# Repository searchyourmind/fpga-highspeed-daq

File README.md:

# FPGA High-Speed DAQ — RTL simulation portfolio

**SystemVerilog · cocotb · Verilator · Python · Yosys · nextpnr (Lattice ECP5)**

A single-clock acquisition pipeline with ready/valid buffering, saturating gain, ring-buffer DMA and packetized host readback. **63 tests pass; 33 end-to-end scenarios match independent expected records.** DDR3 is a **behavioral model**; PCIe is a **custom transaction-level model**, not a hardware endpoint.

The waveform comes from an executed regression. [Full VCD](evidence/core/daq_top.vcd.gz) · [Trace provenance](portfolio/assets/evidence.json)

| Verified result | Evidence |
|---|---|
| **63/63 PASS**, zero failures/skips | 39 pytest + 24 cocotb; [actual clean-checkout log](evidence/core/verify.log) |
| **33/33 MATCH** | 15 baseline + 18 extended scenarios **within** those tests; [results](evidence/core/verification.json) |
| Independent checks detect six injected defects | [Mutation results and coverage limits](docs/VERIFICATION_REVIEW.md) |
| Generic synthesis: 1,447 flip-flops, no latches/loops | [Yosys evidence](evidence/core/synthesis/); 42-cell topological path |
| **ECP5 place and route: 57.3 MHz median Fmax** (5 seeds, LFE5U-25F); meets the 25 MHz board clock | [Board build, critical path, resources](fpga/README.md) |

### ECP5 baseline

The core is placed and routed for the Lattice LFE5U-25F on a [ULX3S board top](fpga/README.md) that takes descriptors over UART and keeps every input live. These are the numbers to beat:

- **Fmax 55.7 / 57.3 / 58.0 MHz** (min / median / max of 5 seeds); 2,017 LUT4, 1,315 FF, 2 block RAMs, 2 multipliers.
- **Critical path:** two hardware multipliers in one cycle, `seq × 73` in `sensor_source` feeding `× gain` in `stream_processor`.
- **DMA throughput:** one memory command in flight, so a word costs latency + 1 cycles to write and latency + 2 to read; 0.03 words per cycle at a 32-cycle latency. [Chart and table](fpga/README.md#dma-throughput-baseline-simulation)

The bitstream builds but has not been run on a board.

### Debugging findings

- **4 KiB crossing:** a packet starting at `0x1ff8` crossed a page. Bound payload length by page remainder; [original failing assertion](evidence/debug/boundary-before-fix.xml) retained.
- **Address boundary:** fixed rejection of the final legal 8-byte record at `2^64−8` by validating the last addressed byte.
- **Delayed delivery:** retained host tag ownership until data consumption, even after RTL completion.
- **False-success runner:** reject failed/stale/empty/skipped JUnit; a real failing fixture verifies the gate. [Review](docs/VERIFICATION_REVIEW.md)

### Reproduce

Requires Docker, Make and Python 3. Run from the repository root:

```sh
make tools
make verify                 # lint, 63 tests / 33 scenarios, generic synthesis
make timing                 # structural checks; no device delays or slack
make fpga-tools && make fpga  # ECP5 synthesis, place and route (5 seeds), bitstream
make fpga-test              # ULX3S board top, driven through its UART pins
make throughput             # DMA words per cycle against memory latency
```

Recorded versions: Verilator 5.040, cocotb 2.0.0, pytest 8.4.2, Yosys 0.33. [Commands, versions and clean-checkout scope](docs/REPRODUCING.md) · [Simulation benchmark](portfolio/assets/benchmarks.png)

### Explore the engineering

[Architecture and RTL modules](docs/architecture.md) · [Verification review](docs/VERIFICATION_REVIEW.md) · [Portfolio summary](portfolio/README.md) · [Resume bullets](docs/RESUME_BULLETS.md) · [Release summary](release/RELEASE_SUMMARY.md)

One descriptor is active at a time; capture finishes before readback. The source honors backpressure. No physical ADC, DDR PHY, real PCIe TLP/LCRC or measured hardware throughput is claimed; the ECP5 timing comes from nextpnr's model, not a board. [Interface contracts](docs/interface_contracts.md) · [Synthesis scope](synthesis/README.md)

### Separate PCB Rev 0.3.1 design study

The [Pi 5 FFC-to-M.2 carrier](hardware/reference_pcie_adapter/README.md) is **not the FPGA DAQ board**. Native CAD checks pass; engineering acceptance remains **FAIL**:

| Requirement | Retained result |
|---|---|
| Voltage: 3.135–3.465 V | 3.130447–3.487610 V; margins **−4.553 / −22.610 mV** |
| Thermal screen: ≤125 °C | **6/24 FAIL**; fine-grid worst **160.303 °C**, margin **−35.303 °C** |
| Differential impedance: 81–99 Ω | Broad high corner **106.126 Ω**, margin **−7.126 Ω** |

These are modeled rejection indicators, not measurements or qualified operating conditions. [All cases and root causes](hardware/reference_pcie_adapter/INDEPENDENT_REVIEW.md) · [Pass/fail matrix](docs/REQUIREMENTS_MATRIX.md). No fabrication, purchases or physical validation. Published **as a simulation portfolio with a separate design study**. Local verification evidence is retained; live CI status is available in [GitHub Actions](https://github.com/searchyourmind/fpga-highspeed-daq/actions).

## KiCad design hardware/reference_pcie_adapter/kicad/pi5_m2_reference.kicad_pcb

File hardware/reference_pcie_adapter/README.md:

# Pi 5 FFC to M.2 M-key reference adapter - Rev 0.3.1

**DESIGN REVIEW DRAFT - NOT RELEASED FOR MANUFACTURE.** This is a separate PCB exercise, not a board implementing the DAQ RTL. No board, FPGA, SSD or Pi was purchased, fabricated, powered or tested.

Read the current [INDEPENDENT_REVIEW.md](INDEPENDENT_REVIEW.md) for retained failures and corrected minimum-copper thermal results. [ENGINEERING_REVIEW.md](ENGINEERING_REVIEW.md) retains the preceding detailed review. The current [four-page review PDF](../../portfolio/Independent_Release_Review.pdf) summarizes both project scopes. [BOM_selected.csv](BOM_selected.csv) records 30 manufacturer part selections, conditional approvals and the legacy FFC hold.

Published [CAD views and all numerical cases](../../evidence/pcb/) are preserved separately from ignored regenerated `outputs/`. The board is frozen; no redesign occurred during portfolio finalization.

## Implemented and checked
- Native KiCad 9 schematic and 80 x 78 mm, four-layer board. 30 electrical references, four board-only mounting holes, M.2 support and a corrected 22 x 42 mm card envelope.
- 424 trace/via objects, two filled inner GND planes plus outer power-area GND spreaders. Eight QFN thermal vias and four added TX return vias.
- **ERC 0, geometric DRC 0, unconnected 0, schematic parity 0.** Pin contracts and saved differential geometry pass. Zero planar pair skew excludes connector/via electrical effects.
- Actual schematic PDF, board SVG, native 3D render and DRAFT-only Gerber/drill exports in `outputs/`. Some 3D bodies are unavailable. Final drill report: 92 plated / 7 unplated holes, including H5 center clearance.
- 108 power DC/AC cases; official TPS62130A nominal and loaded-corner startup/load-event/shutdown models; 126 copper load distributions; 24 thermal cases; actual mechanical/filled-plane checks; 2D field solution with convergence checks. `results/engineering-check-summary.json` separates numerical execution from failed design margins.

## Results that prevent release
| Area | Current conclusion |
|---|---|
| Voltage | Nominal and loaded external-component A transients pass, but conservative composite range 3.130447-3.487610 V exceeds the 3.135-3.465 V target. |
| Heat | Corrected 30 um minimum-copper screen: 6/24 FAIL. Fine-grid worst 160.302515 C, margin -35.302515 C against 125 C. Original 35 um five failures and 159.381 C estimate retained. Extrapolated rejection, not sustainable operation. No 2 A continuous rating. |
| SI | Nominal 93.94 ohm. Broad assumed process corners 83.29-106.13 ohm exceed target. Four width candidates under the original broad assumptions fail; tighter tolerances are not accepted as closure. |
| Components | Real candidate MPNs recorded. MLCC effective capacitance, hot/fault inductor behavior, superseded FFC/cable and final connector approval remain open. |
| Mechanics/assembly | Planar envelope passes. Actual SSD, height tolerances, screw engagement, enclosure and via-in-pad assembly remain open. |

## Electrical scope
External regulated, current-limited 5 V enters J3. The 2 A SSD load is a design stress target, not an approved rating. At 4.65 V input and assumed 85% efficiency, its power-core input budget is approximately 1.684 A. Actual cable/mating contacts require approval. The unkeyed input has no reverse-polarity or hot-plug protection.

U1 is **TPS62130A**, with 31.6k/10k 0.1% feedback (3.328 V nominal), 2.2 uH and two nominal 22 uF output capacitors. The A suffix is required: PG pulls low on EN shutdown while VIN remains present. Its official A-model transient is distinct from the older, separate hypothetical 12 V power-tree experiment.

FFC pins 1/2 feed detection only through 3.6k/6.8k; they do not join EXT_5V. All grounds share the reference plane. PWR_EN has a 100k pulldown. PG drives NC7SB3157 CLKREQ isolation; Q1 gates PERST, Q2/Q3 translate open-drain wake. Full missing-supply and IO sequencing is not qualified. J4 external SUSCLK is DNP by default; a selected SSD must not require it for the baseline.

M.2 host-side pin 69 is grounded as in the official Pi reference. Pi RX_P connects to PETP0 pin 43; Pi TX_P to PERP0 pin 49. No additional AC coupling capacitors are inserted; actual endpoint/cable requirements remain an approval item.

The custom TE land pattern follows G-2199230 Rev B3 sheet 3. **1-2199230-4 is M-key; unprefixed 2199230-4 is E-key and must not be substituted.** The drawing and part-specific current approval are distinct.

## Stackup and SI scope
Reference JLC04161H-3313: nominal 1.6 mm, outer copper 35 um, outer prepreg 99.4 um/Er 4.1, inner copper 15.2 um and core 1.265 mm/Er 4.6. These are preliminary design inputs, not a vendor commitment. Adjacent inner planes reference F.Cu/B.Cu pairs. Trunks use 0.14 mm width / 0.152 mm gap; connector/via breakouts expand.

The new quasi-static 2D solver includes an assumed mask and is a screening result. The old 92.11 ohm empirical formula in `outputs/impedance-estimate.json` is a historical approximation. Neither result establishes connector/cable loss, via 3D behavior, eye diagrams, TDR or PCIe compliance. Actual plane projection has no unintended reference voids; TX ground-return vias are within 0.891 mm of each transition.

## Sources, reproduction and constraints
`design.py` is the electrical source; `build.py` creates native CAD; `apply_routing.py` replays `routing/tracks.json`. `make pcb` checks current CAD. `make pcb-rebuild` explicitly regenerates it; preserve future manual changes first.

`make analysis-tools` builds isolated dependencies. `make pcb-engineering` runs the entire numerical review and creates the review PDF; it can take tens of minutes. `make pcb-engineering-check` checks retained evidence. `make pcb-draft` emits review-only files. No command orders hardware or pushes GitHub.

Detailed sources, failed attempts, limits and next work are in `ENGINEERING_REVIEW.md`, `docs/PROGRESS.md` and `NEXT_SESSION.md`. The actual model files are fetched from TI and excluded from the portable archive. Cadence hands-on remains **NOT COMPLETED**.

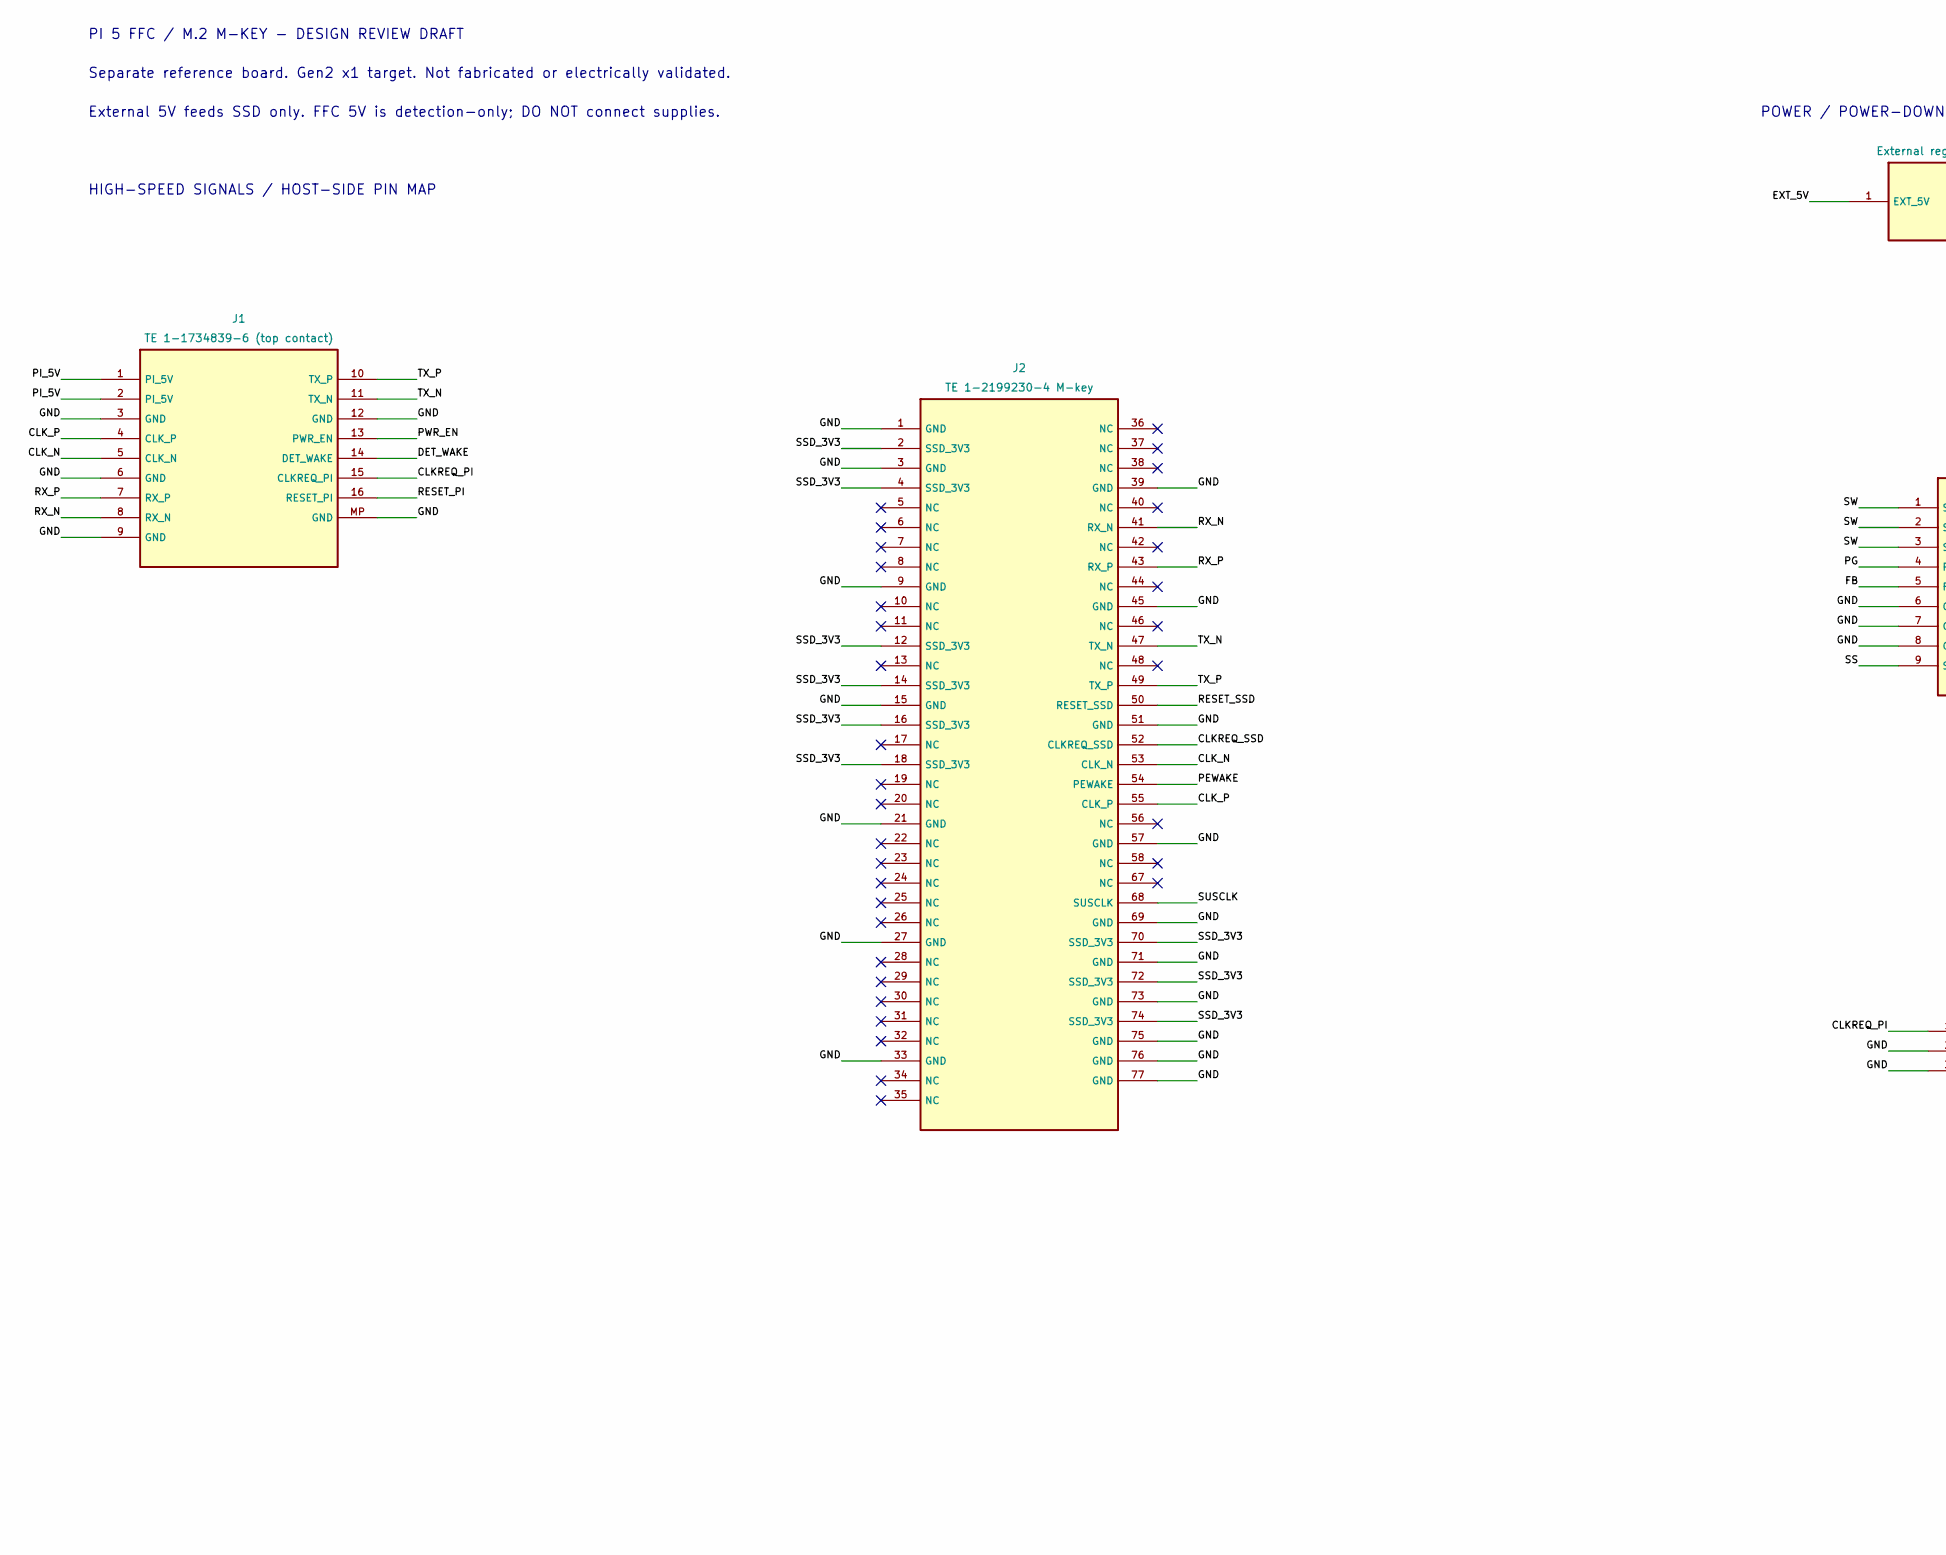
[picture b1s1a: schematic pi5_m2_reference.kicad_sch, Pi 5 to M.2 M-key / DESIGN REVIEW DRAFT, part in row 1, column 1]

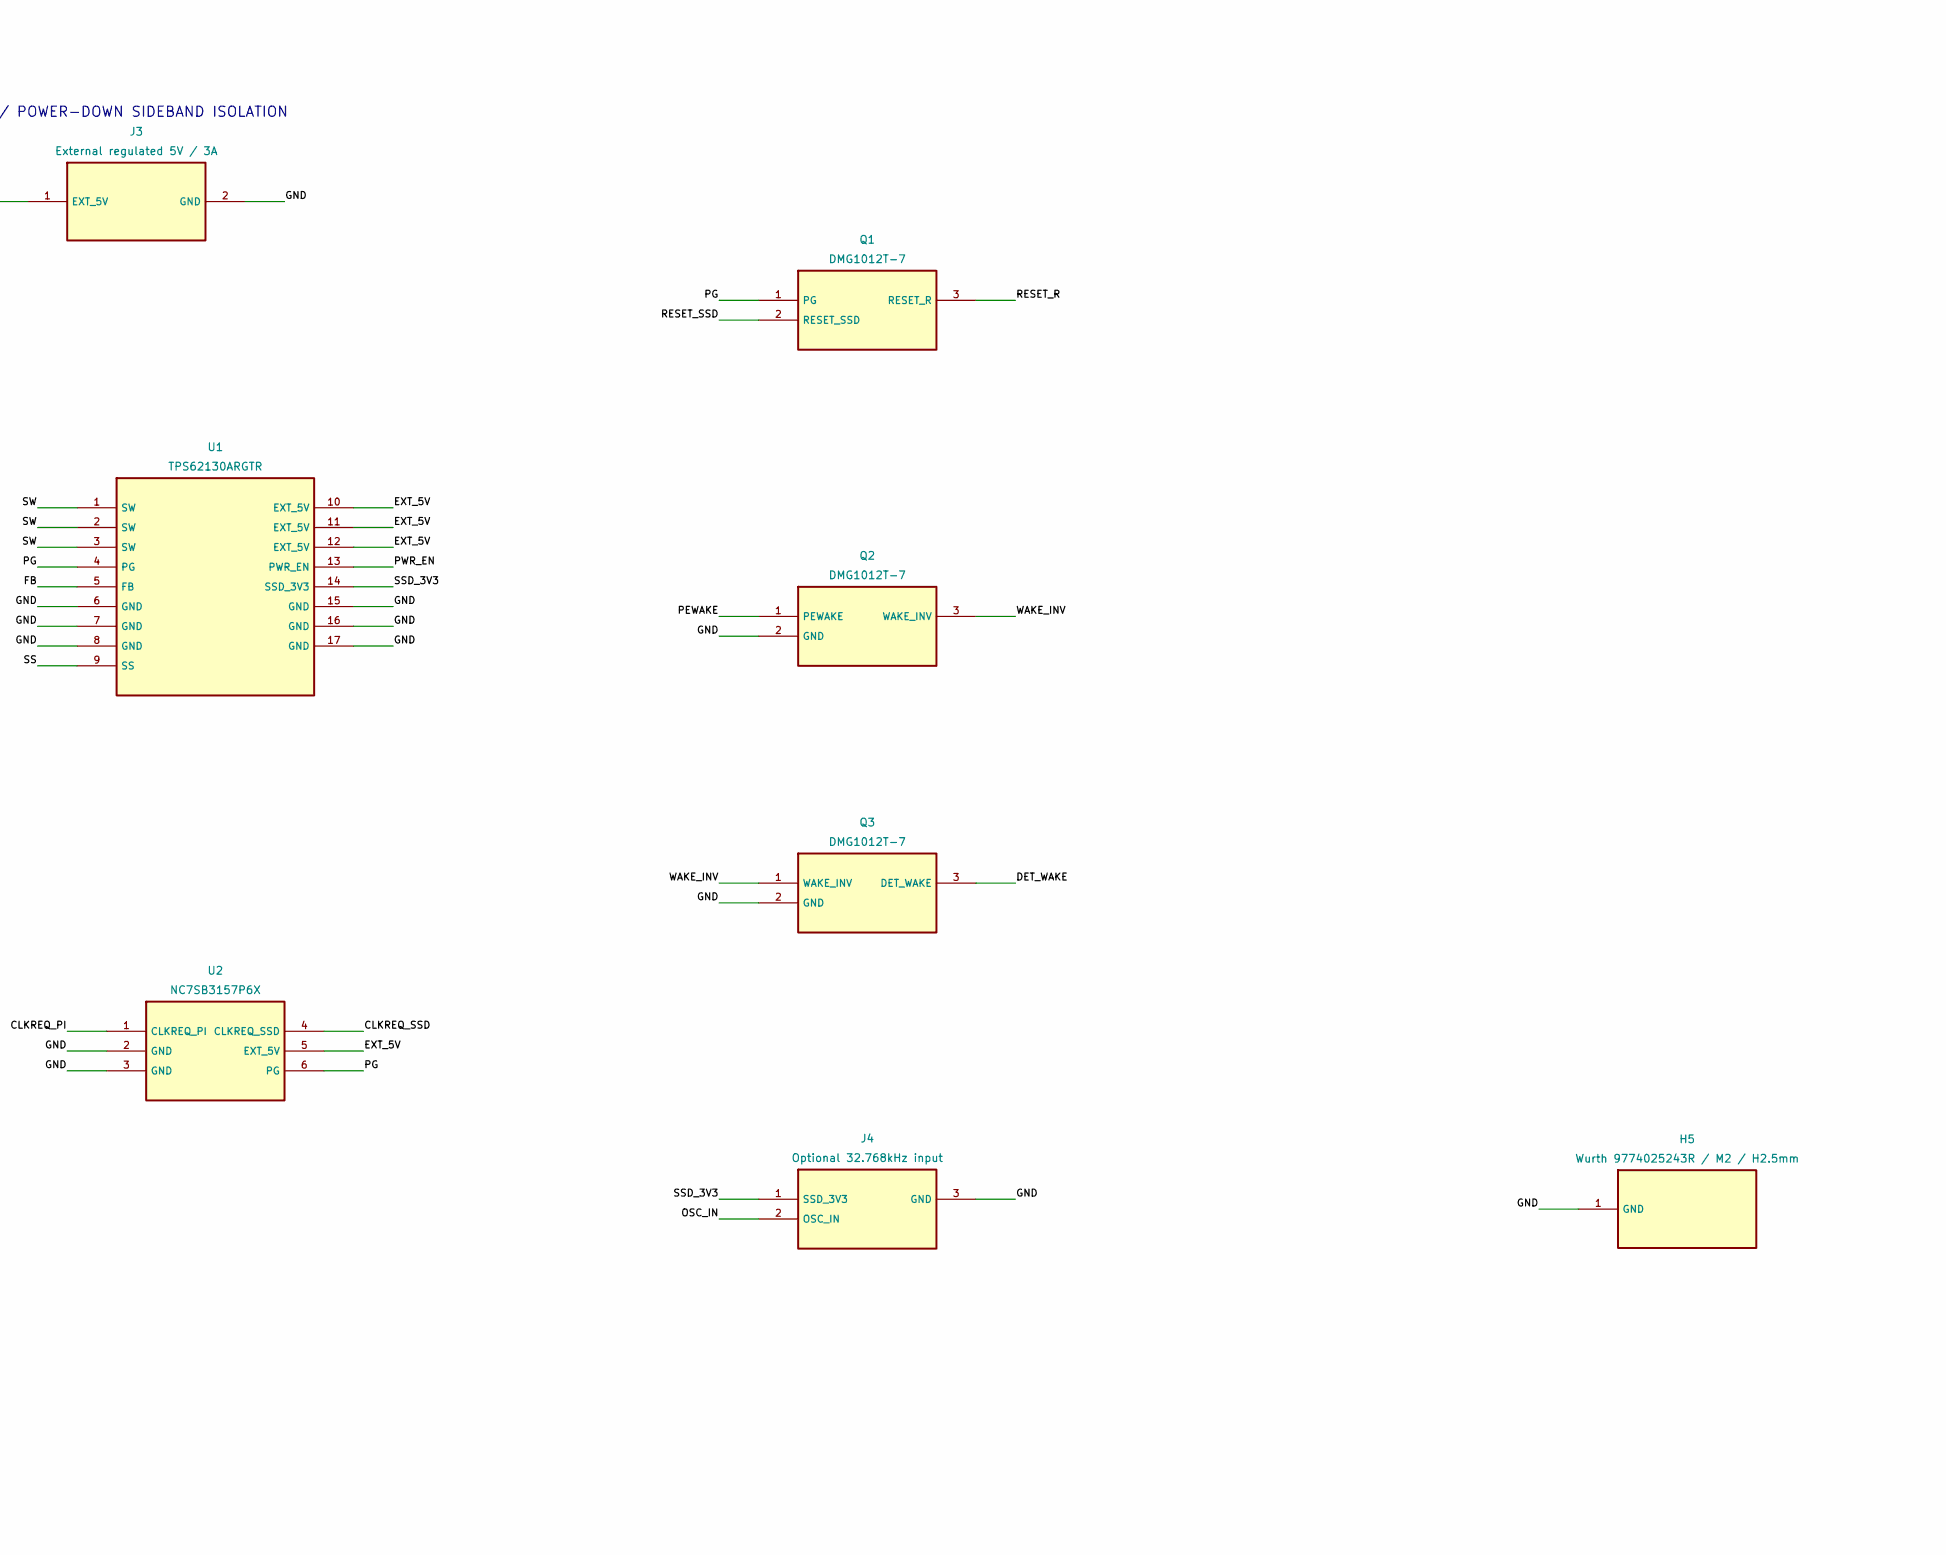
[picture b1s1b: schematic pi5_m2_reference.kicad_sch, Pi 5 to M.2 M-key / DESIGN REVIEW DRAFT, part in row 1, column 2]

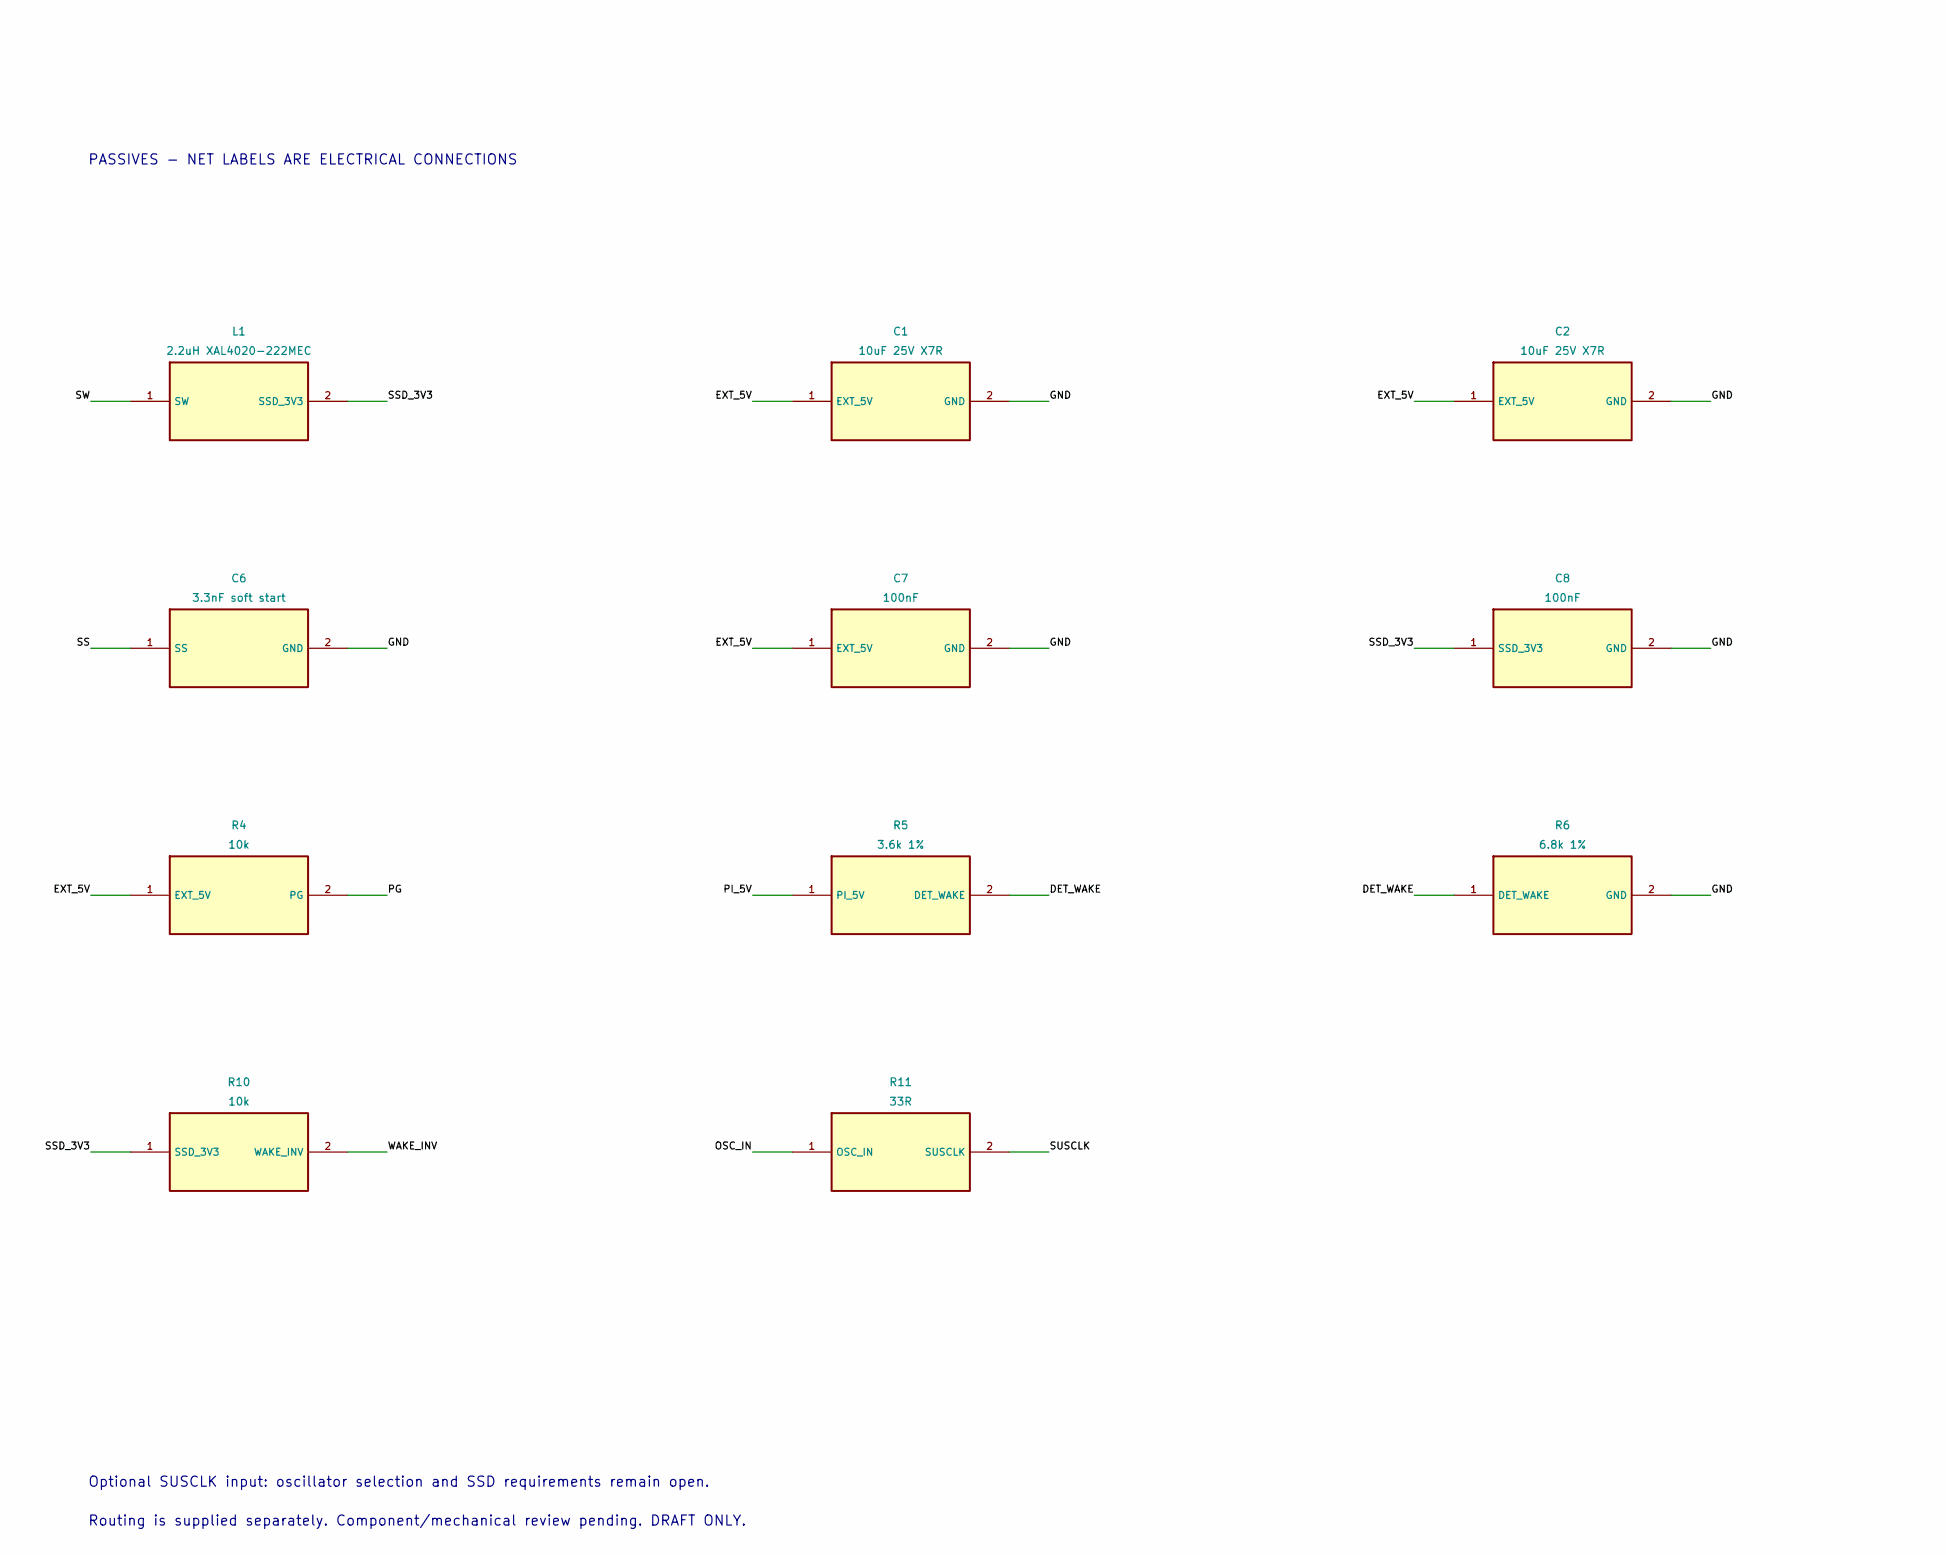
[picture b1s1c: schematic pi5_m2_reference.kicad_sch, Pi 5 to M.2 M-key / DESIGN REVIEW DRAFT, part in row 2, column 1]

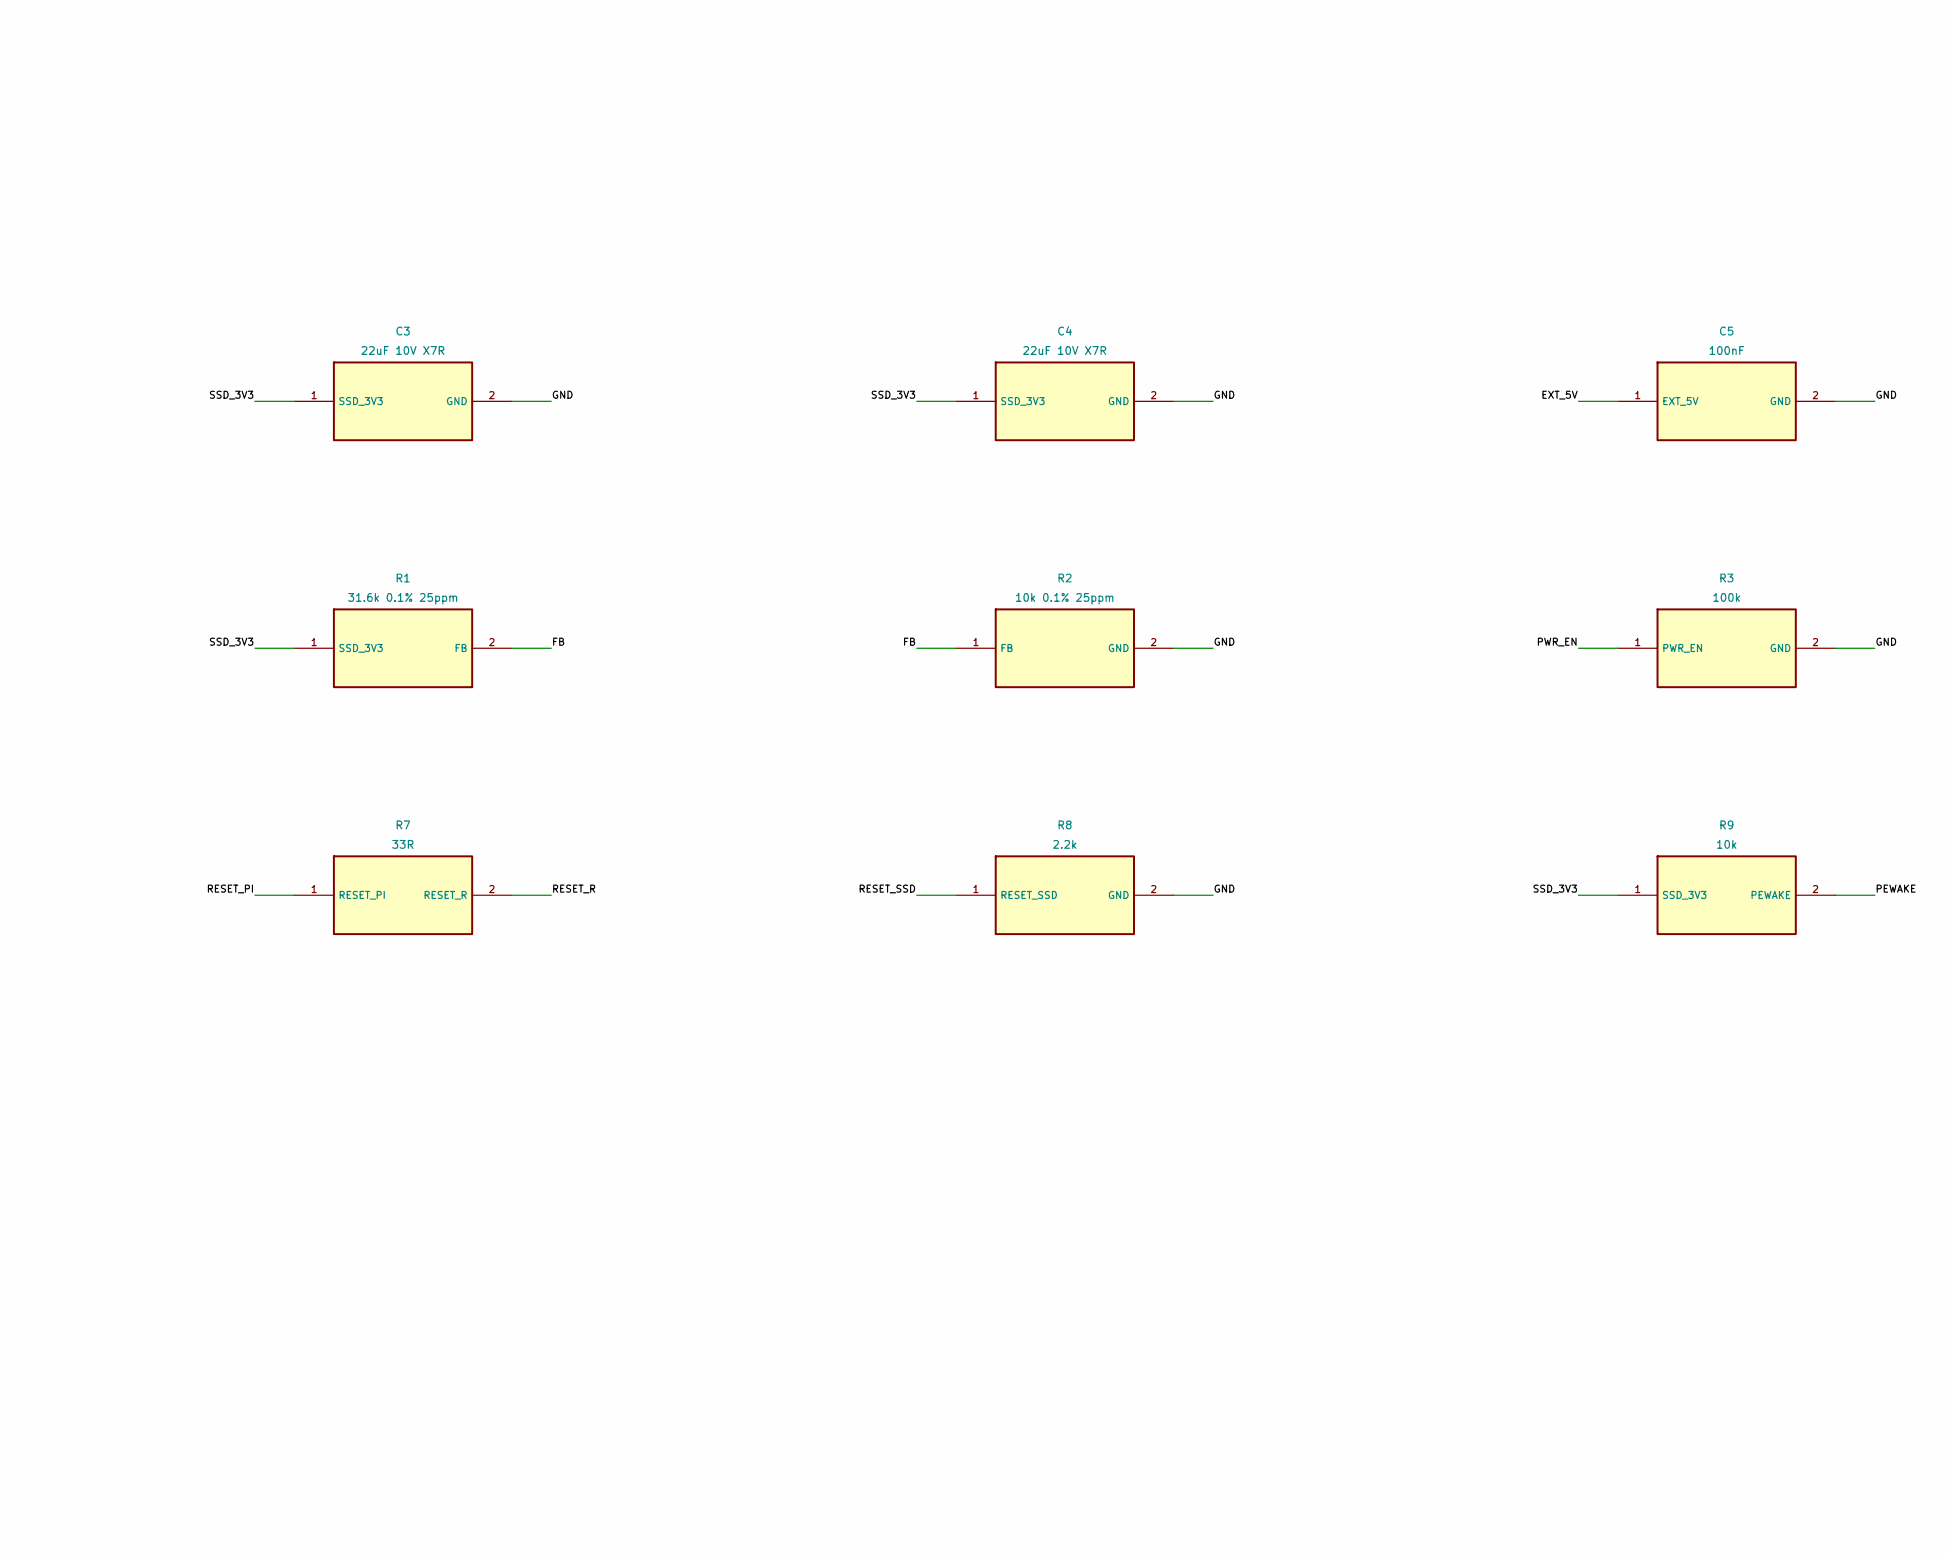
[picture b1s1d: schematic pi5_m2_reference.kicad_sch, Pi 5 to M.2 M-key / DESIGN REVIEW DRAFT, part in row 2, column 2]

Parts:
C1, C2: 10uF 25V X7R; C_1206_3216Metric
C3, C4: 22uF 10V X7R; C_1206_3216Metric
C5, C7, C8: 100nF; C_0402_1005Metric
C6: 3.3nF soft start; C_0402_1005Metric
H5: Wurth 9774025243R / M2 / H2.5mm; Mounting_Wuerth_WA-SMSI-M2_H2.5mm_9774025243
J1: TE 1-1734839-6 (top contact); TE_1-1734839-6_1x16-1MP_P0.5mm_Horizontal
J2: TE 1-2199230-4 M-key; TE_M2_M_1-2199230-4
J3: External regulated 5V / 3A; PinHeader_1x02_P2.54mm_Vertical
J4: Optional 32.768kHz input; PinHeader_1x03_P2.54mm_Vertical
L1: 2.2uH XAL4020-222MEC; L_Coilcraft_XAL4020-XXX
Q1, Q2, Q3: DMG1012T-7; SOT-523
R1: 31.6k 0.1% 25ppm; R_0402_1005Metric
R2: 10k 0.1% 25ppm; R_0402_1005Metric
R3: 100k; R_0402_1005Metric
R4, R9, R10: 10k; R_0402_1005Metric
R5: 3.6k 1%; R_0402_1005Metric
R6: 6.8k 1%; R_0402_1005Metric
R7, R11: 33R; R_0402_1005Metric
R8: 2.2k; R_0402_1005Metric
U1: TPS62130ARGTR; VQFN-16-1EP_3x3mm_P0.5mm_EP1.6x1.6mm
U2: NC7SB3157P6X; SOT-363_SC-70-6

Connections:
/CLKREQ_PI: J1.15 (CLKREQ_PI), U2.1 (CLKREQ_PI)
/CLKREQ_SSD: J2.52 (CLKREQ_SSD), U2.4 (CLKREQ_SSD)
/CLK_N: J1.5 (CLK_N), J2.53 (CLK_N)
/CLK_P: J1.4 (CLK_P), J2.55 (CLK_P)
/DET_WAKE: J1.14 (DET_WAKE), Q3.3 (DET_WAKE), R5.2 (DET_WAKE), R6.1 (DET_WAKE)
/EXT_5V: C1.1 (EXT_5V), C2.1 (EXT_5V), C5.1 (EXT_5V), C7.1 (EXT_5V), J3.1 (EXT_5V), R4.1 (EXT_5V), U1.10 (EXT_5V), U1.11 (EXT_5V), U1.12 (EXT_5V), U2.5 (EXT_5V)
/FB: R1.2 (FB), R2.1 (FB), U1.5 (FB)
/GND: C1.2 (GND), C2.2 (GND), C3.2 (GND), C4.2 (GND), C5.2 (GND), C6.2 (GND), C7.2 (GND), C8.2 (GND), H5.1, J1.3 (GND), J1.6 (GND), J1.9 (GND), J1.12 (GND), J1.MP (GND), J2.1 (GND), J2.3 (GND), J2.9 (GND), J2.15 (GND), J2.21 (GND), J2.27 (GND), J2.33 (GND), J2.39 (GND), J2.45 (GND), J2.51 (GND), J2.57 (GND), J2.69 (GND), J2.71 (GND), J2.73 (GND), J2.75 (GND), J2.76 (GND), J2.77 (GND), J3.2 (GND), J4.3 (GND), Q2.2 (GND), Q3.2 (GND), R2.2 (GND), R3.2 (GND), R6.2 (GND), R8.2 (GND), U1.6 (GND), U1.7 (GND), U1.8 (GND), U1.15 (GND), U1.16 (GND), U1.17 (GND), U2.2 (GND), U2.3 (GND)
/OSC_IN: J4.2 (OSC_IN), R11.1 (OSC_IN)
/PEWAKE: J2.54 (PEWAKE), Q2.1 (PEWAKE), R9.2 (PEWAKE)
/PG: Q1.1 (PG), R4.2 (PG), U1.4 (PG), U2.6 (PG)
/PI_5V: J1.1 (PI_5V), J1.2 (PI_5V), R5.1 (PI_5V)
/PWR_EN: J1.13 (PWR_EN), R3.1 (PWR_EN), U1.13 (PWR_EN)
/RESET_PI: J1.16 (RESET_PI), R7.1 (RESET_PI)
/RESET_R: Q1.3 (RESET_R), R7.2 (RESET_R)
/RESET_SSD: J2.50 (RESET_SSD), Q1.2 (RESET_SSD), R8.1 (RESET_SSD)
/RX_N: J1.8 (RX_N), J2.41 (RX_N)
/RX_P: J1.7 (RX_P), J2.43 (RX_P)
/SS: C6.1 (SS), U1.9 (SS)
/SSD_3V3: C3.1 (SSD_3V3), C4.1 (SSD_3V3), C8.1 (SSD_3V3), J2.2 (SSD_3V3), J2.4 (SSD_3V3), J2.12 (SSD_3V3), J2.14 (SSD_3V3), J2.16 (SSD_3V3), J2.18 (SSD_3V3), J2.70 (SSD_3V3), J2.72 (SSD_3V3), J2.74 (SSD_3V3), J4.1 (SSD_3V3), L1.2 (SSD_3V3), R1.1 (SSD_3V3), R9.1 (SSD_3V3), R10.1 (SSD_3V3), U1.14 (SSD_3V3)
/SUSCLK: J2.68 (SUSCLK), R11.2 (SUSCLK)
/SW: L1.1 (SW), U1.1 (SW), U1.2 (SW), U1.3 (SW)
/TX_N: J1.11 (TX_N), J2.47 (TX_N)
/TX_P: J1.10 (TX_P), J2.49 (TX_P)
/WAKE_INV: Q2.3 (WAKE_INV), Q3.1 (WAKE_INV), R10.2 (WAKE_INV)

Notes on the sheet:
PI 5 FFC / M.2 M-KEY - DESIGN REVIEW DRAFT
Separate reference board. Gen2 x1 target. Not fabricated or electrically validated.
External 5V feeds SSD only. FFC 5V is detection-only; DO NOT connect supplies.
HIGH-SPEED SIGNALS / HOST-SIDE PIN MAP
POWER / POWER-DOWN SIDEBAND ISOLATION
PASSIVES - NET LABELS ARE ELECTRICAL CONNECTIONS
Optional SUSCLK input: oscillator selection and SSD requirements remain open.
Routing is supplied separately. Component/mechanical review pending. DRAFT ONLY.

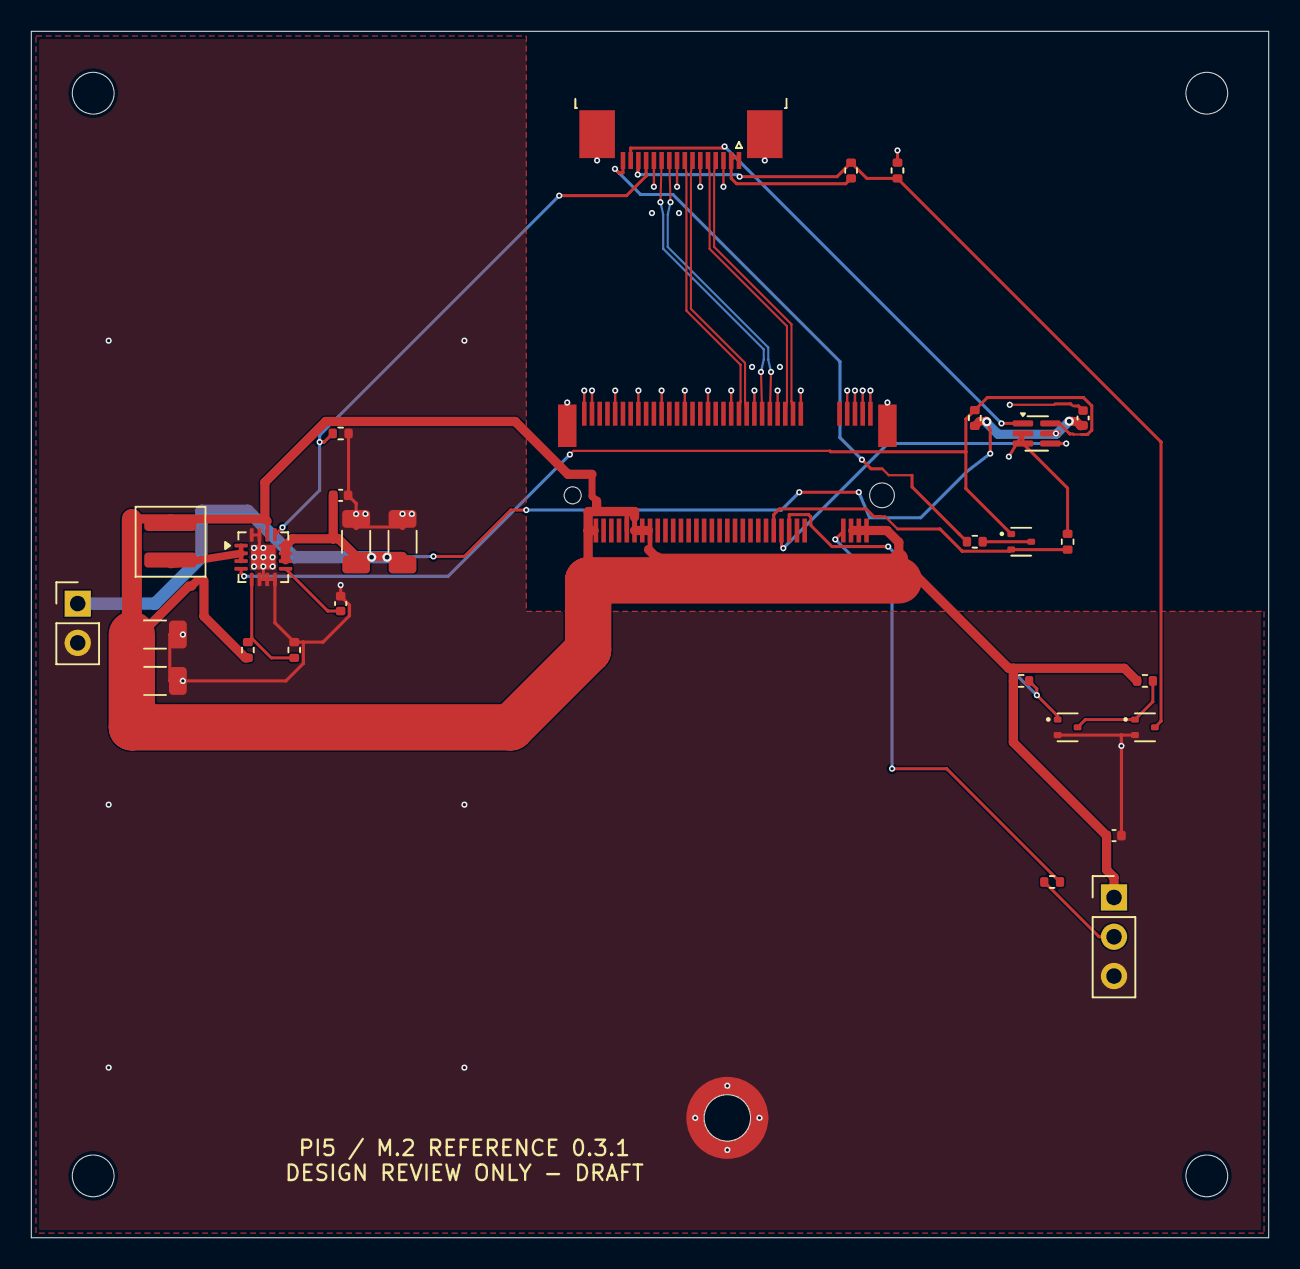
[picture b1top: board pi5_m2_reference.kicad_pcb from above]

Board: 4 copper layers, 80.0 x 78.0 mm, 34 parts (0 on the bottom side), 25 nets.

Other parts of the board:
H1, H2, H3, H4: M2.5 board mount; MountingHole_2.7mm_M2.5

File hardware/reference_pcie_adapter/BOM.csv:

Reference,Value,Footprint,Note
J1,TE 1-1734839-6 (top contact),Connector_FFC-FPC:TE_1-1734839-6_1x16-1MP_P0.5mm_Horizontal,Superseded part; replacement qualification required
J2,TE 1-2199230-4 M-key,DAQ:TE_M2_M_1-2199230-4,Custom footprint from TE G-2199230 B3 sheet 3; review before release
J3,External regulated 5V / 3A,Connector_PinHeader_2.54mm:PinHeader_1x02_P2.54mm_Vertical,No reverse-polarity or hot-plug protection: external current-limited source only
U1,TPS62130ARGTR,Package_DFN_QFN:VQFN-16-1EP_3x3mm_P0.5mm_EP1.6x1.6mm,3.328V nominal; <=2A SSD; 8 thermal vias; assembly review pending
U2,NC7SB3157P6X,Package_TO_SOT_SMD:SOT-363_SC-70-6,S=0 grounds SSD CLKREQ; S=1 connects host
Q1,DMG1012T-7,Package_TO_SOT_SMD:SOT-523,
Q2,DMG1012T-7,Package_TO_SOT_SMD:SOT-523,
Q3,DMG1012T-7,Package_TO_SOT_SMD:SOT-523,
J4,Optional 32.768kHz input,Connector_PinHeader_2.54mm:PinHeader_1x03_P2.54mm_Vertical,External oscillator footprint/part not selected; SSD-dependent requirement remains open
H5,Wurth 9774025243R / M2 / H2.5mm,Mounting_Wuerth:Mounting_Wuerth_WA-SMSI-M2_H2.5mm_9774025243,SMT support; height and insertion datum require mating-card confirmation
L1,2.2uH XAL4020-222MEC,Inductor_SMD:L_Coilcraft_XAL4020-XXX,
C1,10uF 25V X7R,Capacitor_SMD:C_1206_3216Metric,
C2,10uF 25V X7R,Capacitor_SMD:C_1206_3216Metric,
C3,22uF 10V X7R,Capacitor_SMD:C_1206_3216Metric,
C4,22uF 10V X7R,Capacitor_SMD:C_1206_3216Metric,
C5,100nF,Capacitor_SMD:C_0402_1005Metric,
C6,3.3nF soft start,Capacitor_SMD:C_0402_1005Metric,
C7,100nF,Capacitor_SMD:C_0402_1005Metric,
C8,100nF,Capacitor_SMD:C_0402_1005Metric,
R1,31.6k 0.1% 25ppm,Resistor_SMD:R_0402_1005Metric,
R2,10k 0.1% 25ppm,Resistor_SMD:R_0402_1005Metric,
R3,100k,Resistor_SMD:R_0402_1005Metric,
R4,10k,Resistor_SMD:R_0402_1005Metric,
R5,3.6k 1%,Resistor_SMD:R_0402_1005Metric,
R6,6.8k 1%,Resistor_SMD:R_0402_1005Metric,
R7,33R,Resistor_SMD:R_0402_1005Metric,
R8,2.2k,Resistor_SMD:R_0402_1005Metric,
R9,10k,Resistor_SMD:R_0402_1005Metric,
R10,10k,Resistor_SMD:R_0402_1005Metric,
R11,33R,Resistor_SMD:R_0402_1005Metric,
